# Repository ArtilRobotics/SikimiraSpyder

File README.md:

# SikimiraSpyder
a repo for dev a escaparete

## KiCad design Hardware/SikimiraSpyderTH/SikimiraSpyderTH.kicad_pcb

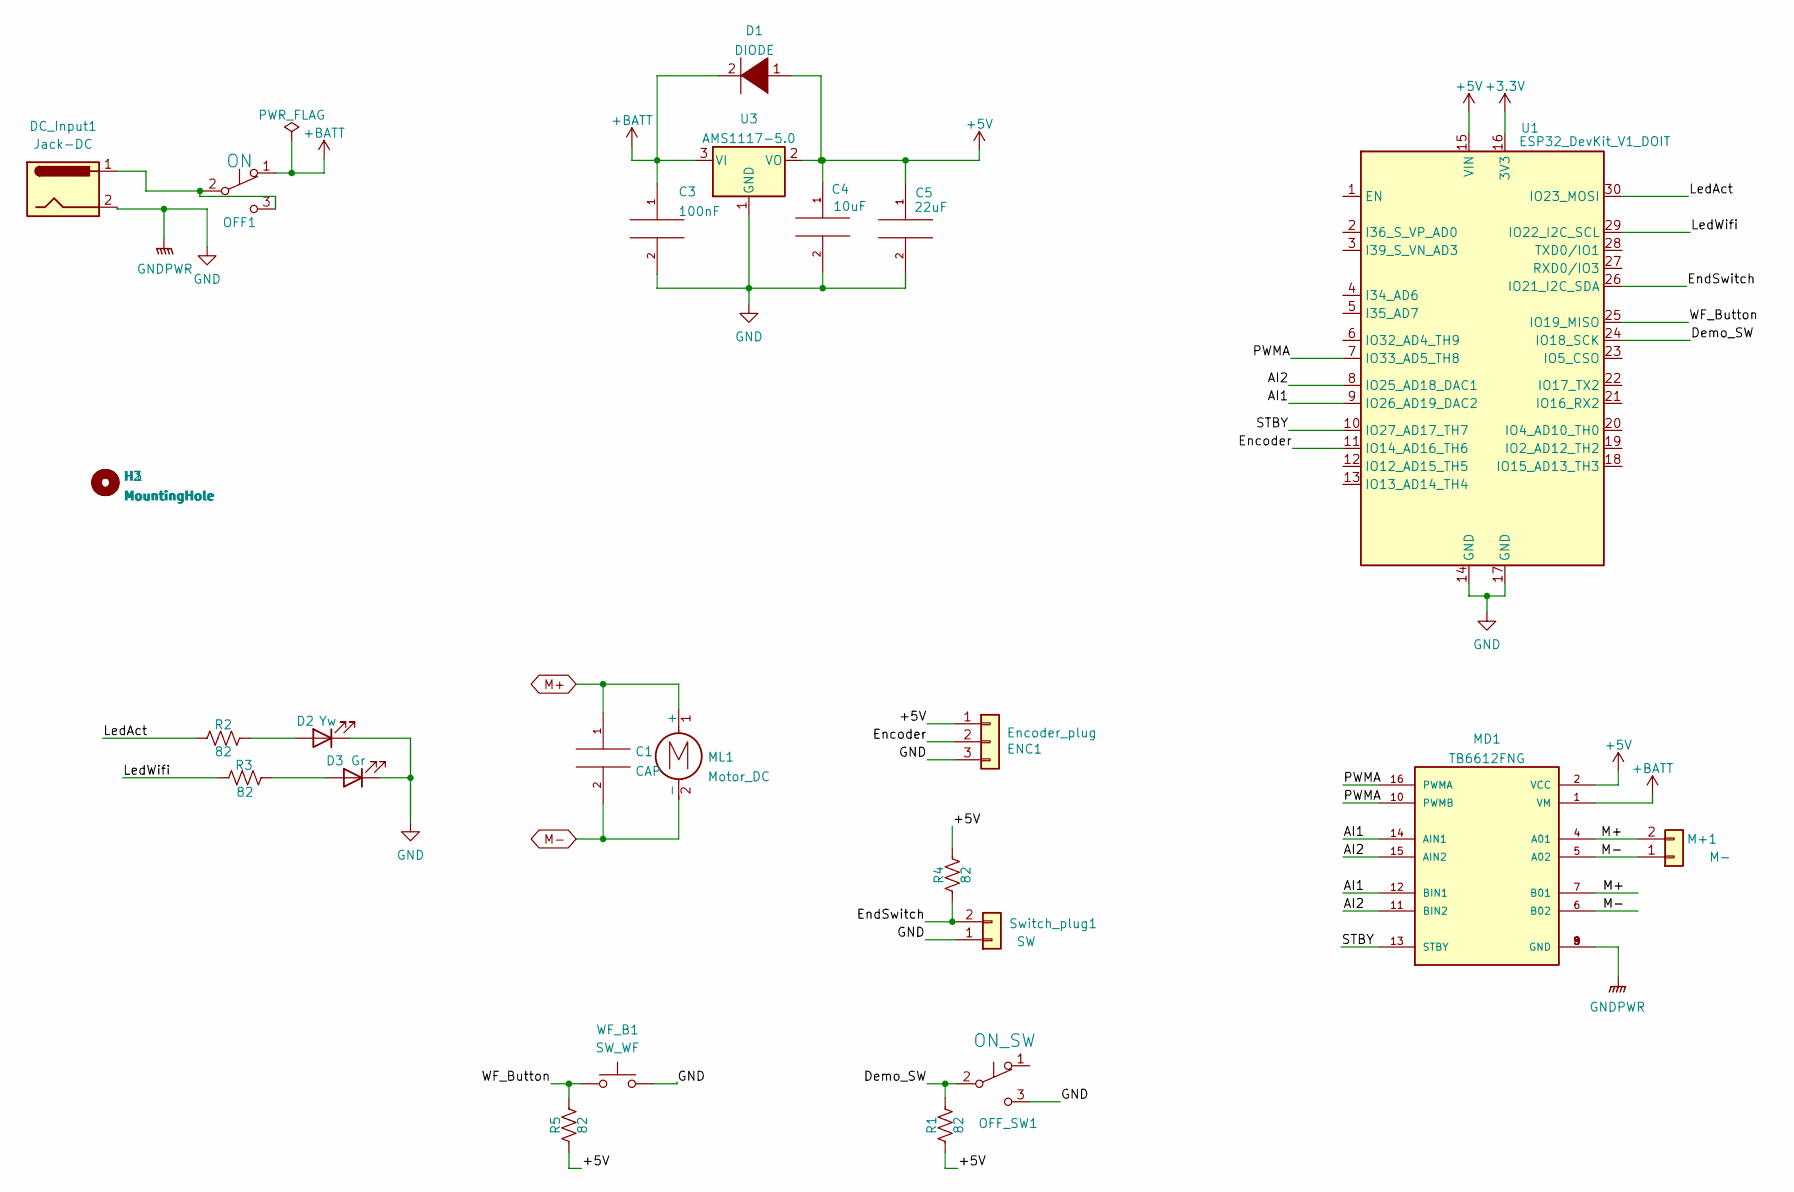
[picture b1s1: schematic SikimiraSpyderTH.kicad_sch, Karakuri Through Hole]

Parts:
C1: CAP; C_Disc_D3.0mm_W2.0mm_P2.50mm
C3: 100nF; C_0805_2012Metric_Pad1.18x1.45mm_HandSolder
C4: 10uF; C_0805_2012Metric_Pad1.18x1.45mm_HandSolder
C5: 22uF; C_0805_2012Metric_Pad1.18x1.45mm_HandSolder
D1: DIODE; D_0805_2012Metric_Pad1.15x1.40mm_HandSolder
D2: Yw; LED_D5.0mm
D3: Gr; LED_D5.0mm
DC_Input1: Jack-DC; BarrelJack_Horizontal
ENC1: Encoder_plug; JST_EH_B3B-EH-A_1x03_P2.50mm_Vertical
H1, H2, H3: MountingHole; MountingHole_3.2mm_M3_ISO7380_Pad
M+1: M-; TerminalBlock_bornier-2_P5.08mm
MD1: TB6612FNG; MODULE_TB6612FNG Motor; PARTREV 11-13-17
ML1: Motor_DC; NetTie-2_SMD_Pad0.5mm
OFF1: ON; SW_Slide_1P2T_CK_OS102011MS2Q
OFF_SW1: ON_SW; SW_Slide_1P2T_CK_OS102011MS2Q
R1, R2, R3, R4, R5: 82; R_Axial_DIN0207_L6.3mm_D2.5mm_P10.16mm_Horizontal
Switch_plug1: SW; JST_PH_B2B-PH-K_1x02_P2.00mm_Vertical
U1: ESP32_DevKit_V1_DOIT; esp32_devkit_v1_doit
U3: AMS1117-5.0; SOT-223-3_TabPin2
WF_B1: SW_WF; SW_Tactile_SPST_Angled_PTS645Vx39-2LFS

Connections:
+3V3: U1.16 (3V3)
+5V: C4.1, C5.1, D1.1 (K), ENC1.1, MD1.2 (VCC), R1.1, R4.2, R5.1, U1.15 (VIN), U3.2 (VO)
+BATT: C3.1, D1.2 (A), MD1.1 (VM), OFF1.1 (A), U3.3 (VI)
/AI1: MD1.12 (BIN1), MD1.14 (AIN1), U1.9 (IO26_AD19_DAC2)
/AI2: MD1.11 (BIN2), MD1.15 (AIN2), U1.8 (IO25_AD18_DAC1)
/Demo_SW: OFF_SW1.2 (B), R1.2, U1.24 (IO18_SCK)
/Encoder: ENC1.2, U1.11 (IO14_AD16_TH6)
/EndSwitch: R4.1, Switch_plug1.2, U1.26 (IO21_I2C_SDA)
/LedAct: R2.1, U1.30 (IO23_MOSI)
/LedWifi: R3.1, U1.29 (IO22_I2C_SCL)
/PWMA: MD1.10 (PWMB), MD1.16 (PWMA), U1.7 (IO33_AD5_TH8)
/STBY: MD1.13 (STBY), U1.10 (IO27_AD17_TH7)
/WF_Button: R5.2, U1.25 (IO19_MISO), WF_B1.2
GND: C3.2, C4.2, C5.2, D2.1 (K), D3.1 (K), DC_Input1.2, ENC1.3, MD1.3 (GND), MD1.8 (GND), MD1.9 (GND), OFF_SW1.3 (C), Switch_plug1.1, U1.14 (GND), U1.17 (GND), U3.1 (GND), WF_B1.1
M+: C1.1, M+1.2, MD1.4 (A01), MD1.7 (B01), ML1.1 (+)
M-: C1.2, M+1.1, MD1.5 (A02), MD1.6 (B02), ML1.2 (-)
unnamed: D2.2 (A), R2.2
unnamed: D3.2 (A), R3.2
unnamed: DC_Input1.1, OFF1.2 (B), OFF1.3 (C)

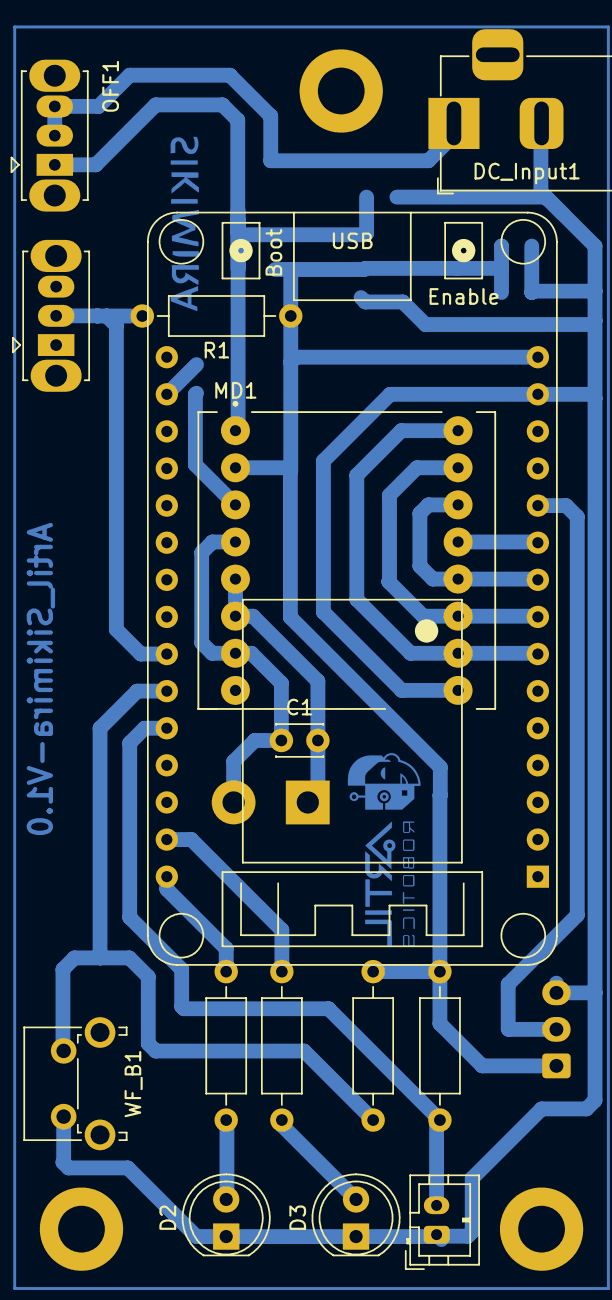
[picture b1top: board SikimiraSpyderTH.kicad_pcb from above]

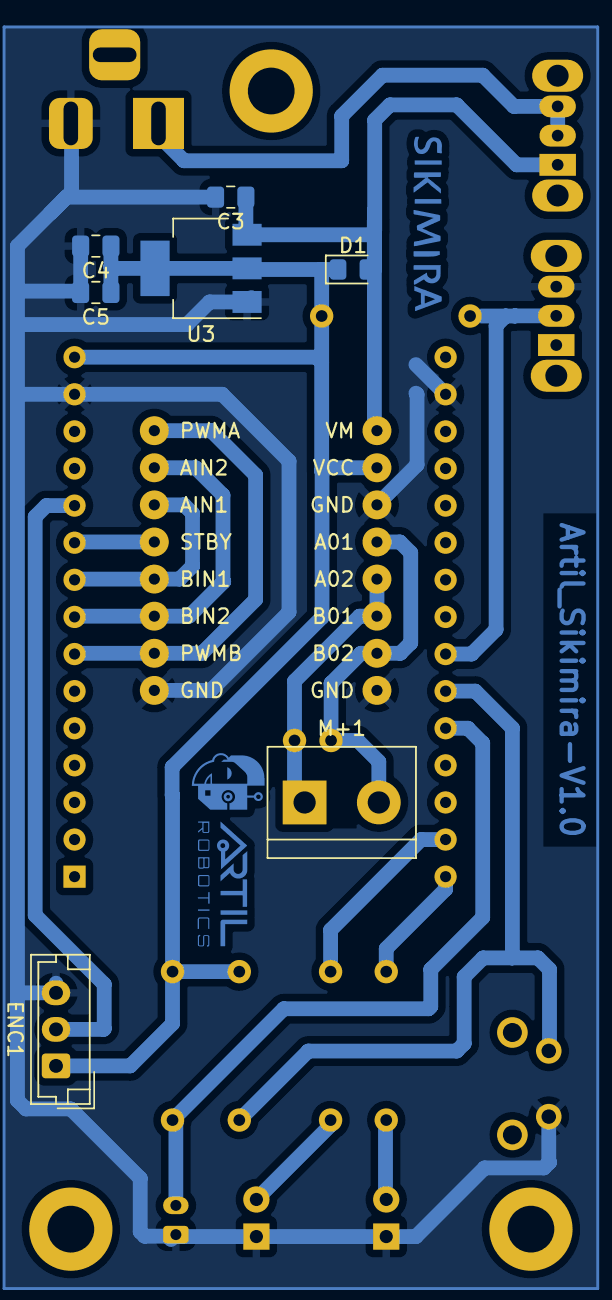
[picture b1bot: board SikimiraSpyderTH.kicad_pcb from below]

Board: 2 copper layers, 25 parts (7 on the bottom side), 18 nets.

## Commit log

2022-09-13 agregue platform io
2022-09-14 agregue librerias utiles desde Karakuri.
2022-09-14 Agregue mi nombre
2022-09-14 Agregar Funcion Home
2022-09-15 Agregado Control de Tiempo V1 (Solo en el Main)
2022-09-15 PruebaBrazo
2022-09-16 Conexión Wifi mediante BT
2022-09-17 Funciones de Encoder incluidas en main.
2022-09-18 Traslado de funciones desde main a librerias.
2022-09-18 Modified Main
2022-09-19 Comentarios main limpiados
2022-09-19 aumento de tiempo de conexión a 1min
2022-09-20 Set Values from app; Include funtions on Actions.
2022-10-03 Branch to FInal test
2022-10-03 Pruebas Movimiento 1
2022-10-04 Testing
2022-10-04 Pruebas Movimiento Slider
2022-10-04 Slider Testing
2022-10-05 Orden de Carpetas y PCB base desde KarakuriTH
2022-10-05 quite del repositorio los backup de KiCAD
2022-10-05 formateo
2022-10-06 Spider Completado
2022-10-31 Modificaciones Tiempo offline - Wifi Reconect
2022-11-01 PCB Creada, Cambio de pines
2022-11-01 Cambiado de pines y corregido PCB
2022-11-21 Pcbs Update
2022-12-09 arduino uno configuration
2022-12-20 Codigo Adaptado
